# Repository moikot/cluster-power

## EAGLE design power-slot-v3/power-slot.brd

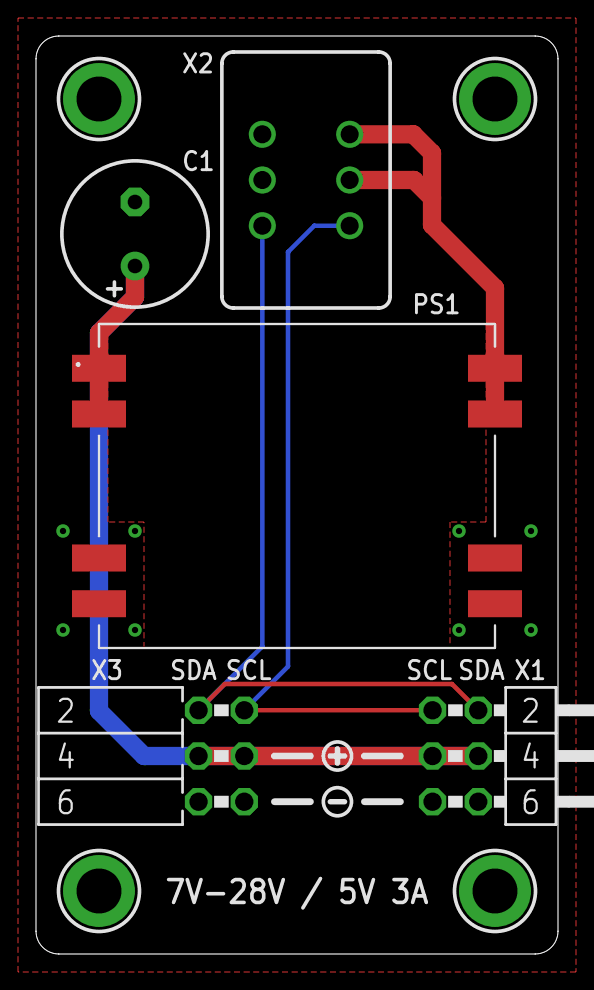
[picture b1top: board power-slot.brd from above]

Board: 2 copper layers, 29.0 x 51.0 mm, 11 parts (0 on the bottom side), 5 nets.

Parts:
C1: CELEC_3.5MM_8MM
PS1: K8801
U$1, U$2, U$3, U$4: MOUNTINGHOLE2.5_THICK; MOUNTINGHOLE_2.5_PLATED_THICK
U$5: SYMBOL_PLUS
U$6: SYMBOL_MINUS
X1: CON-MA03-2MA03-2W; MA03-2W
X2: FE3-2-CARDEDGE-0.1
X3: FE06-2W

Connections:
+5V: PS1.5, PS1.6, X2.4, X2.6
GND: C1.-, PS1.3, PS1.4, PS1.7, PS1.8, X1.5, X1.6, X2.3, X2.5, X3.5, X3.6
PWR: C1.+, PS1.1, PS1.2, X1.3, X1.4, X3.3, X3.4
SCL: X1.1, X2.2, X3.1
SDA: X1.2, X2.1, X3.2

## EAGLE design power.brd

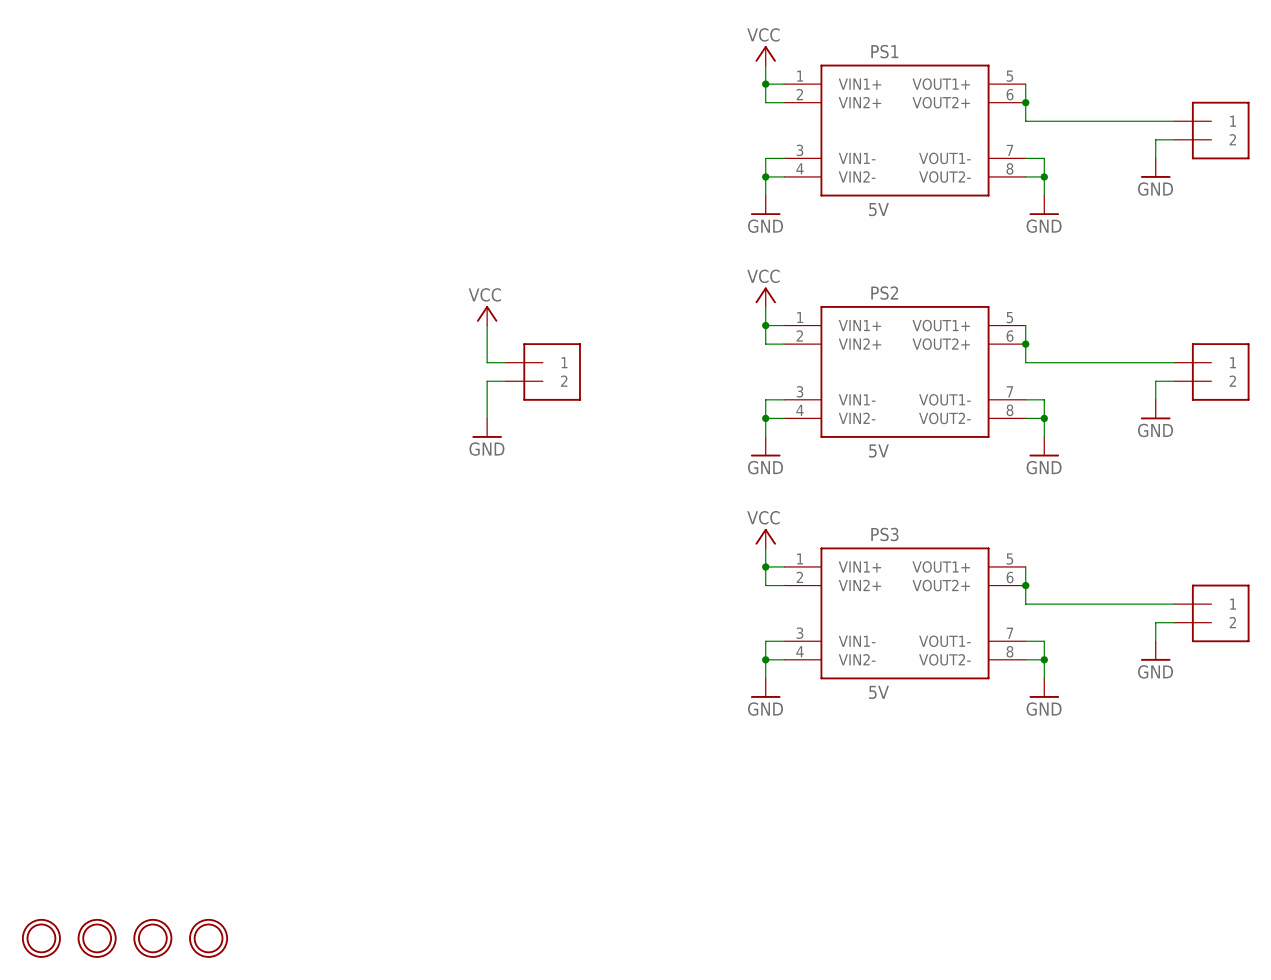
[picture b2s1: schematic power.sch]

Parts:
J1, J2, J3, J4: 1X2-3.5MM
PS1, PS2, PS3: 5V; K8801
U$1, U$2, U$3, U$4: MICROBUILDER_MOUNTINGHOLE2.5; MICROBUILDER_MOUNTINGHOLE_2.5_PLATED

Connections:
GND: J1.2, J2.2, J3.2, J4.2, PS1.3 (VIN1-), PS1.4 (VIN2-), PS1.7 (VOUT1-), PS1.8 (VOUT2-), PS2.3 (VIN1-), PS2.4 (VIN2-), PS2.7 (VOUT1-), PS2.8 (VOUT2-), PS3.3 (VIN1-), PS3.4 (VIN2-), PS3.7 (VOUT1-), PS3.8 (VOUT2-)
unnamed: J3.1, PS2.5 (VOUT1+), PS2.6 (VOUT2+)
unnamed: J4.1, PS3.5 (VOUT1+), PS3.6 (VOUT2+)
unnamed: J2.1, PS1.5 (VOUT1+), PS1.6 (VOUT2+)
VCC: J1.1, PS1.1 (VIN1+), PS1.2 (VIN2+), PS2.1 (VIN1+), PS2.2 (VIN2+), PS3.1 (VIN1+), PS3.2 (VIN2+)

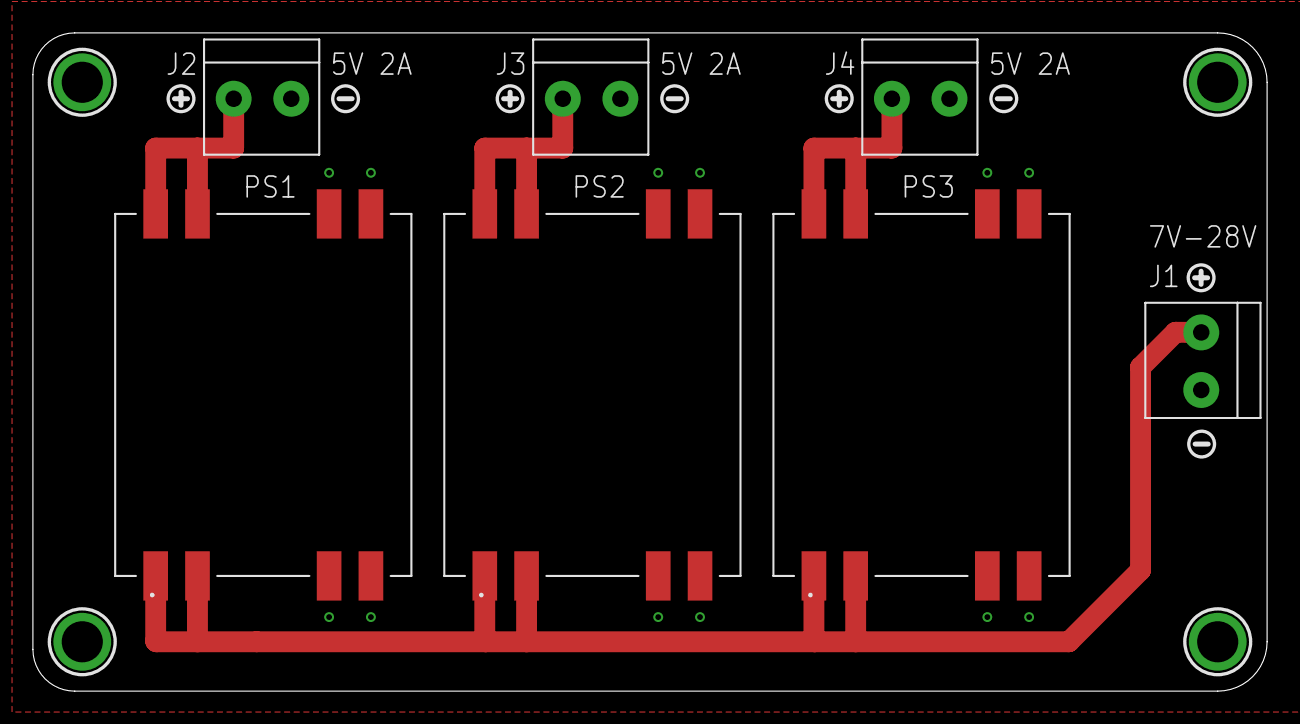
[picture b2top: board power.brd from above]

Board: 2 copper layers, 75.0 x 40.0 mm, 19 parts (0 on the bottom side), 5 nets.

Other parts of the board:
U$5, U$7, U$9, U$11: SYMBOL_PLUS
U$6, U$8, U$10, U$12: SYMBOL_MINUS

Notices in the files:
parts and their libraries:
microbuilder: This work is placed in the public domain, and may be freely used for commercial and non-commercial work with the following conditions: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
